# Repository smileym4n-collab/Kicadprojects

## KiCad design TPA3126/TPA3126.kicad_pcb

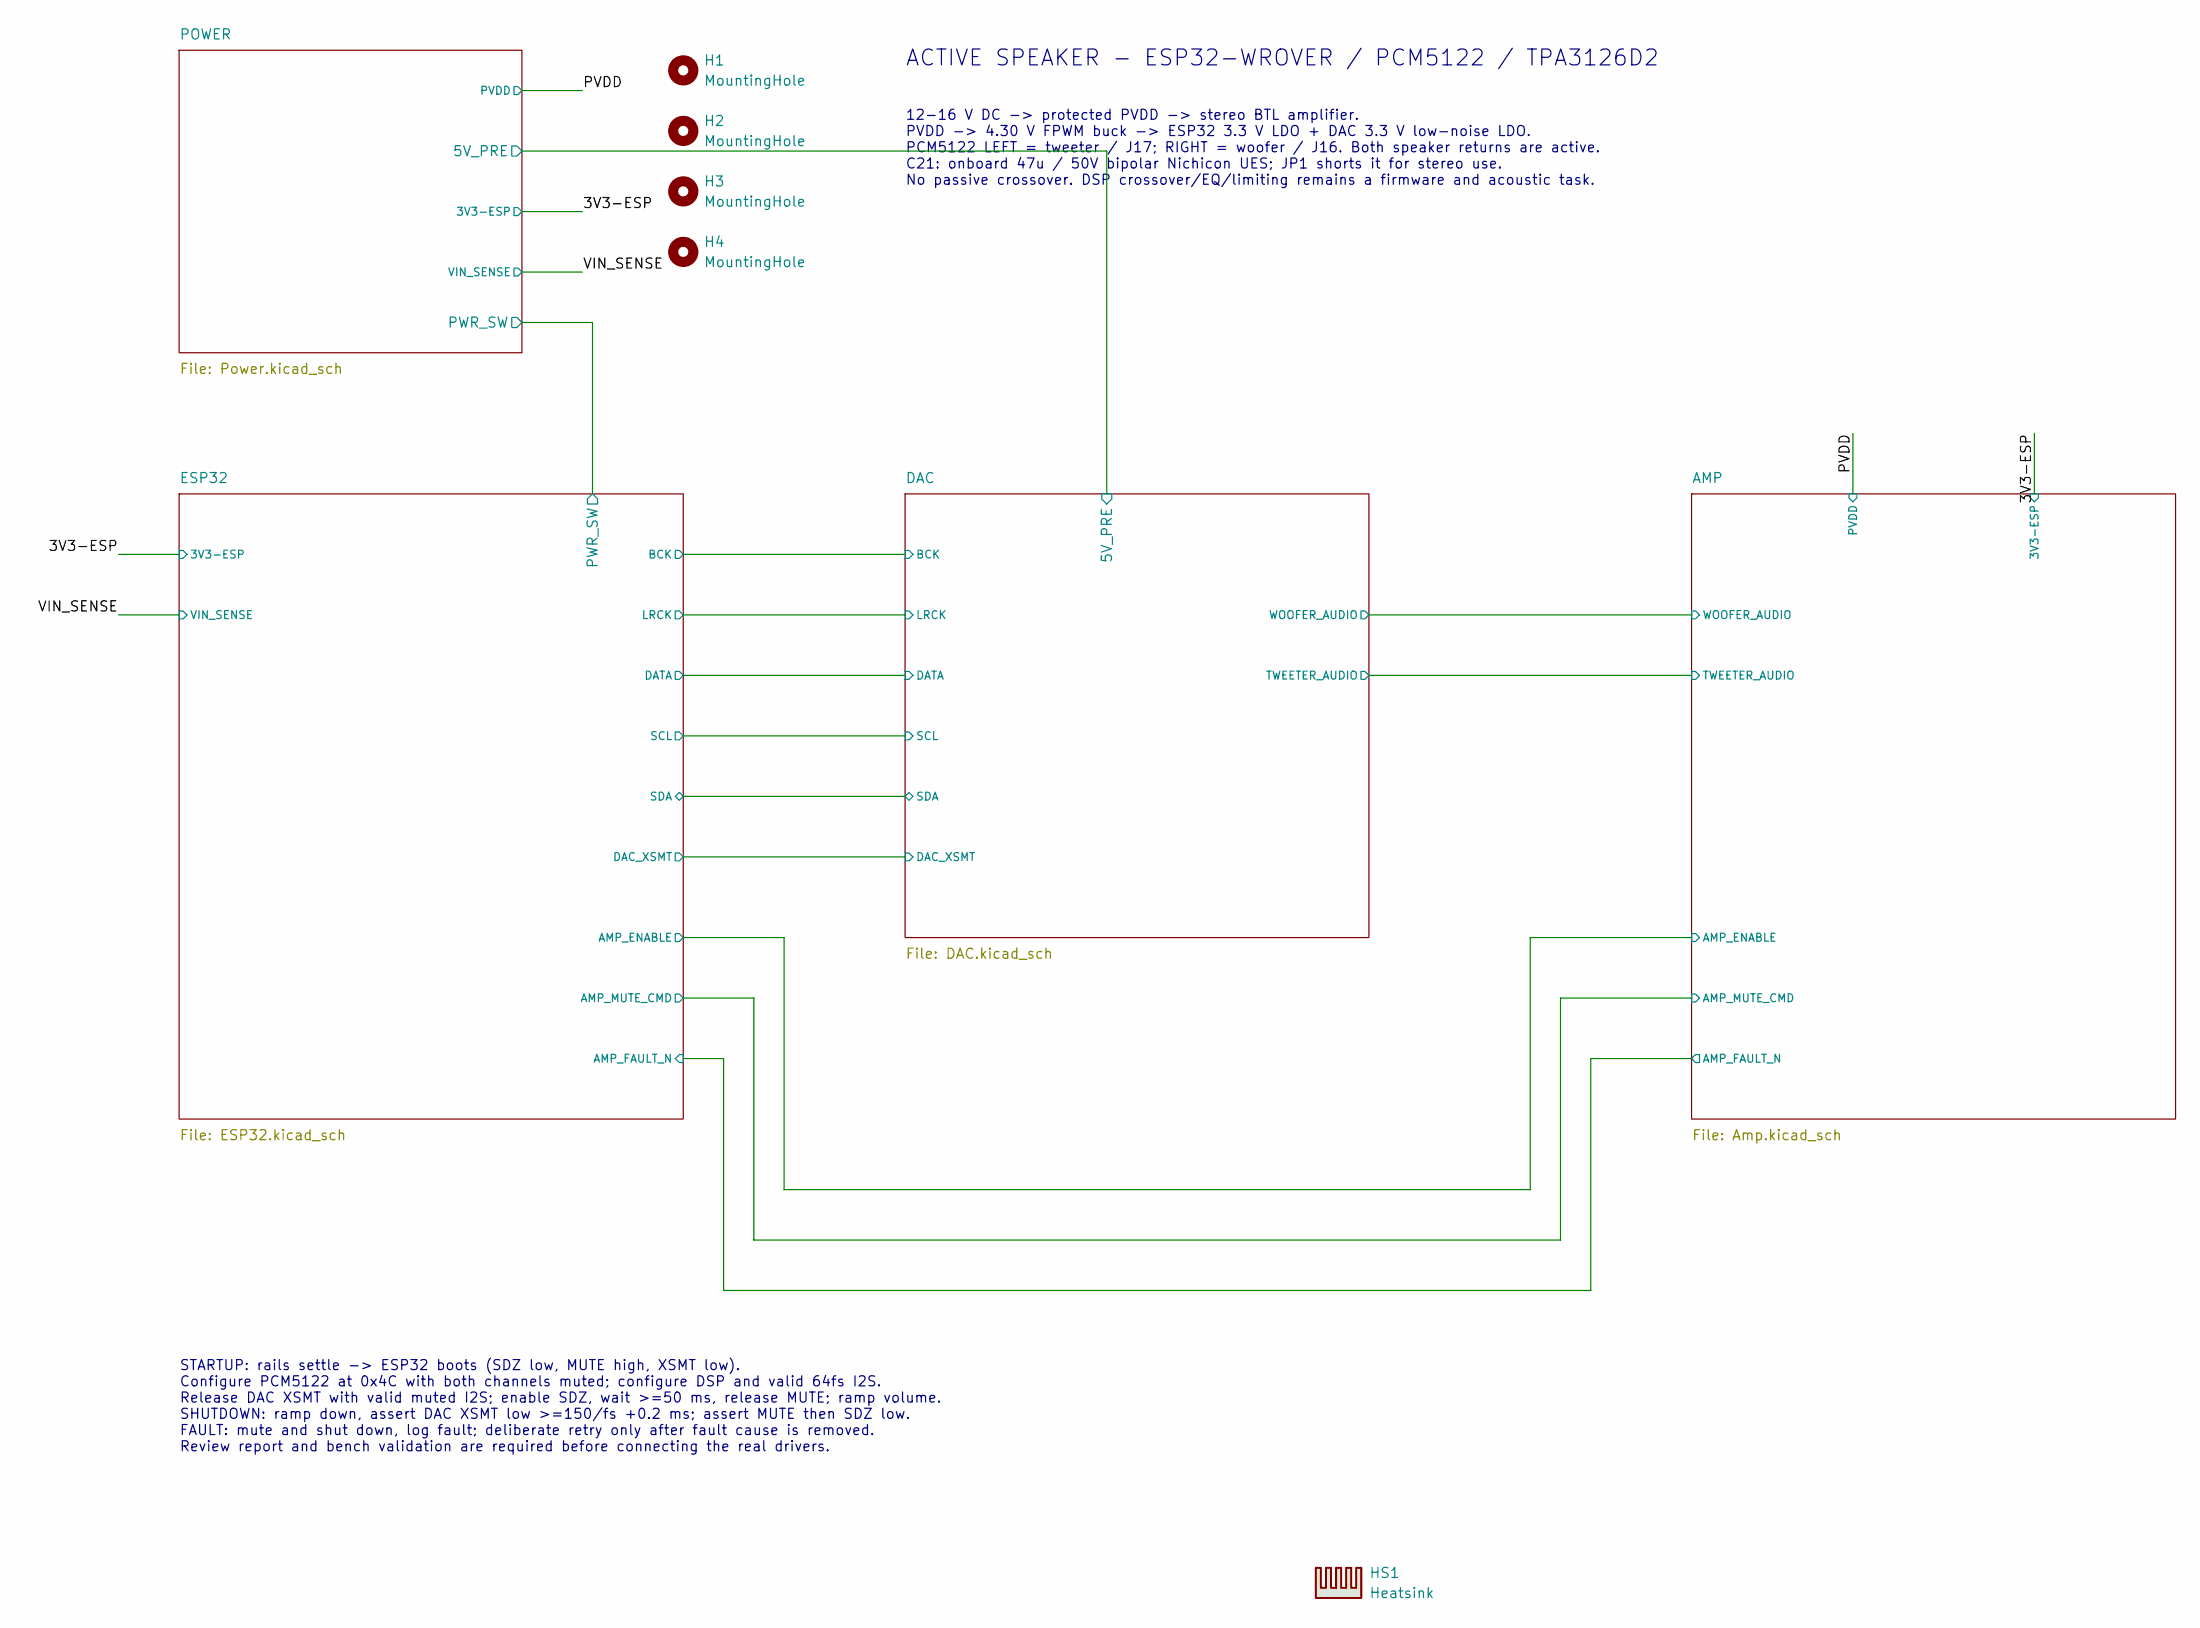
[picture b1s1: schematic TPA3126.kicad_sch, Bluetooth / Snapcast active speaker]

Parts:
H1, H2, H3, H4: MountingHole; MountingHole_3.2mm_M3
HS1: Heatsink; Heatsink_ATS_ATS-TI1OP-521-C1-R1_50x13.9mm_H25mm_P40mm; MPN ATS-TI1OP-521-C1-R1

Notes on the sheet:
STARTUP: rails settle -> ESP32 boots (SDZ low, MUTE high, XSMT low). Configure PCM5122 at 0x4C with both channels muted; configure DSP and valid 64fs I2S. Release DAC XSMT with valid muted I2S; enable SDZ, wait >=50 ms, release MUTE; ramp volume. SHUTDOWN: ramp down, assert DAC XSMT low >=150/fs +0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
ACTIVE SPEAKER - ESP32-WROVER / PCM5122 / TPA3126D2
12-16 V DC -> protected PVDD -> stereo BTL amplifier. PVDD -> 4.30 V FPWM buck -> ESP32 3.3 V LDO + DAC 3.3 V low-noise LDO. PCM5122 LEFT = tweeter / J17; RIGHT = woofer / J16. Both speaker returns are active. C21: onboard 47u / 50V bipolar Nichicon UES; JP1 shorts it for stereo use. No passive cro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

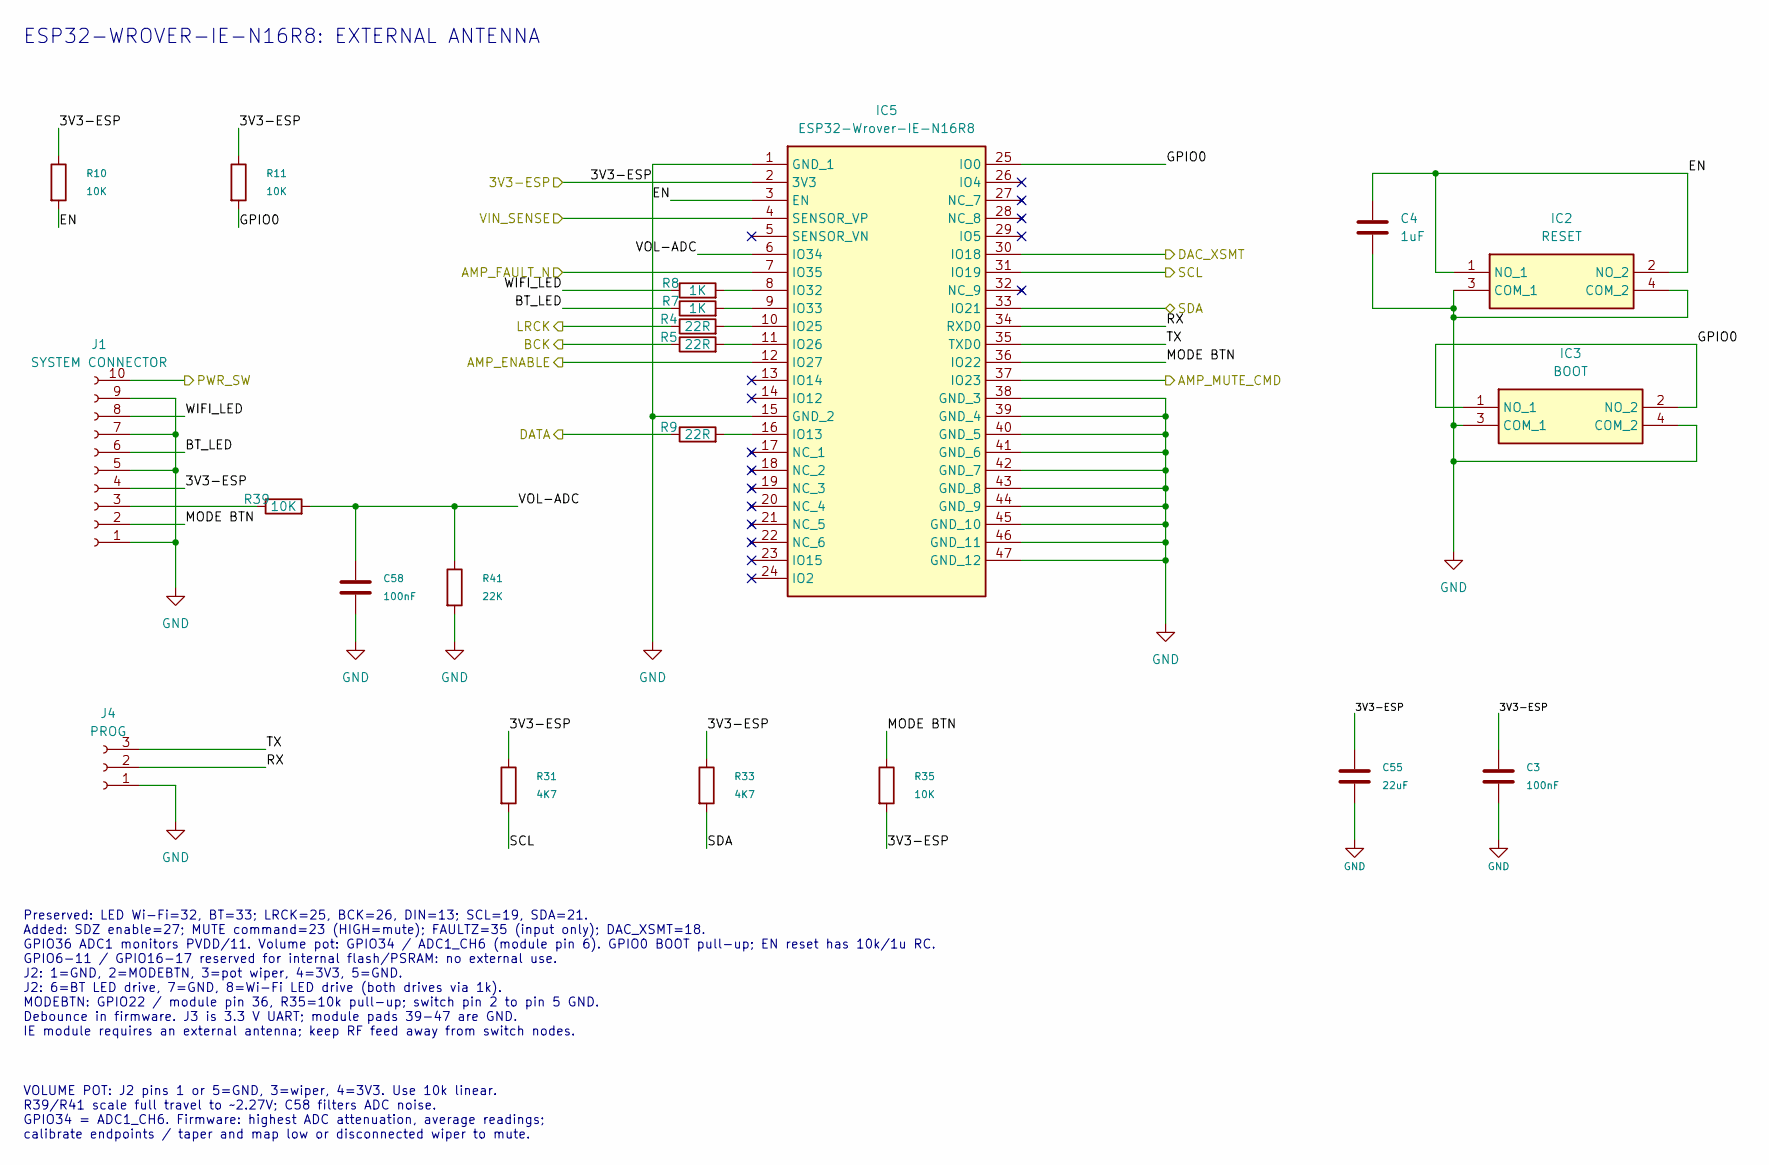
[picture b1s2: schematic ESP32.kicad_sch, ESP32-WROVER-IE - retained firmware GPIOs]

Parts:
C3, C58: 100nF; C_1206_3216Metric_Pad1.33x1.80mm_HandSolder; MPN C1206C104K5RACTU
C4: 1uF; C_1206_3216Metric_Pad1.33x1.80mm_HandSolder; MPN CL31B105KBHNFNE
C55: 22uF; C_1206_3216Metric_Pad1.33x1.80mm_HandSolder; MPN CL31A226KAHNNNE
IC2: RESET; TS026650BK100SCRD; Mouser Part Number 179-TS026650BK100SCR
IC3: BOOT; TS026650BK100SCRD; Mouser Part Number 179-TS026650BK100SCR
IC5: ESP32-Wrover-IE-N16R8; ESP32-WROVER-IE-N16R8; Mouser Part Number 356-ESP32WRVIE2864UC
J1: SYSTEM CONNECTOR; JST_XH_B10B-XH-A_1x10_P2.50mm_Vertical
J4: PROG; PinHeader_1x03_P2.54mm_Vertical
R4, R5, R9: 22R; R_0603_1608Metric_Pad0.98x0.95mm_HandSolder; MPN RK73B1JTTD220J
R7, R8: 1K; R_0805_2012Metric_Pad1.20x1.40mm_HandSolder; Manufacturer_Part_Number RMCF0805FT1K00
R10, R11, R35: 10K; R_0603_1608Metric_Pad0.98x0.95mm_HandSolder; Manufacturer_Part_Number RC0603FR-0710KL
R31, R33: 4K7; R_0805_2012Metric_Pad1.20x1.40mm_HandSolder; MPN RMCF0805FT4K70
R39: 10K; R_0805_2012Metric_Pad1.20x1.40mm_HandSolder; MPN RK73B2ATTD103J
R41: 22K; R_0805_2012Metric_Pad1.20x1.40mm_HandSolder; MPN RR1220P-223-D

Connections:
/3V3-ESP: C3.1, C55.1, IC5.2 (3V3), J1.4, R10.1, R11.1, R31.1, R33.1, R35.2; also elsewhere on the board
/AMP/AMP_ENABLE: IC5.12 (IO27); also elsewhere on the board
/AMP/AMP_FAULT_N: IC5.7 (IO35); also elsewhere on the board
/AMP/AMP_MUTE_CMD: IC5.37 (IO23); also elsewhere on the board
/DAC/BCK: R5.1; also elsewhere on the board
/DAC/DAC_XSMT: IC5.30 (IO18); also elsewhere on the board
/DAC/DATA: R9.1; also elsewhere on the board
/DAC/LRCK: R4.1; also elsewhere on the board
/ESP32/BT_LED: J1.6, R7.1
/ESP32/EN: C4.1, IC2.1 (NO_1), IC2.2 (NO_2), IC5.3 (EN), R10.2
/ESP32/GPIO0: IC3.1 (NO_1), IC3.2 (NO_2), IC5.25 (IO0), R11.2
/ESP32/MODE BTN: IC5.36 (IO22), J1.2, R35.1
/ESP32/PWR_SW: J1.10; also elsewhere on the board
/ESP32/RX: IC5.34 (RXD0), J4.2
/ESP32/SCL: IC5.31 (IO19), R31.2; also elsewhere on the board
/ESP32/SDA: IC5.33 (IO21), R33.2; also elsewhere on the board
/ESP32/TX: IC5.35 (TXD0), J4.3
/ESP32/VOL-ADC: C58.1, IC5.6 (IO34), R39.2, R41.1
/ESP32/WIFI_LED: J1.8, R8.1
/VIN_SENSE: IC5.4 (SENSOR_VP); also elsewhere on the board
GND: C3.2, C4.2, C55.2, C58.2, IC2.3 (COM_1), IC2.4 (COM_2), IC3.3 (COM_1), IC3.4 (COM_2), IC5.1 (GND_1), IC5.15 (GND_2), IC5.38 (GND_3), IC5.39 (GND_4), IC5.40 (GND_5), IC5.41 (GND_6), IC5.42 (GND_7), IC5.43 (GND_8), IC5.44 (GND_9), IC5.45 (GND_10), IC5.46 (GND_11), IC5.47 (GND_12), J1.1, J1.5, J1.7, J1.9, J4.1, R41.2; also elsewhere on the board
unnamed: IC5.16 (IO13), R9.2
unnamed: IC5.10 (IO25), R4.2
unnamed: IC5.11 (IO26), R5.2
unnamed: IC5.8 (IO32), R8.2
unnamed: IC5.9 (IO33), R7.2
unnamed: J1.3, R39.1

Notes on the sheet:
ESP32-WROVER-IE-N16R8: EXTERNAL ANTENNA
VOLUME POT: J2 pins 1 or 5=GND, 3=wiper, 4=3V3. Use 10k linear. R39/R41 scale full travel to ~2.27V; C58 filters ADC noise. GPIO34 = ADC1_CH6. Firmware: highest ADC attenuation, average readings; calibrate endpoints / taper and map low or disconnected wiper to mute.
Preserved: LED Wi-Fi=32, BT=33; LRCK=25, BCK=26, DIN=13; SCL=19, SDA=21. Added: SDZ enable=27; MUTE command=23 (HIGH=mute); FAULTZ=35 (input only); DAC_XSMT=18. GPIO36 ADC1 monitors PVDD/11. Volume pot: GPIO34 / ADC1_CH6 (module pin 6). GPIO0 BOOT pull-up; EN reset has 10k/1u RC. GPIO6-11 / GPIO16-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

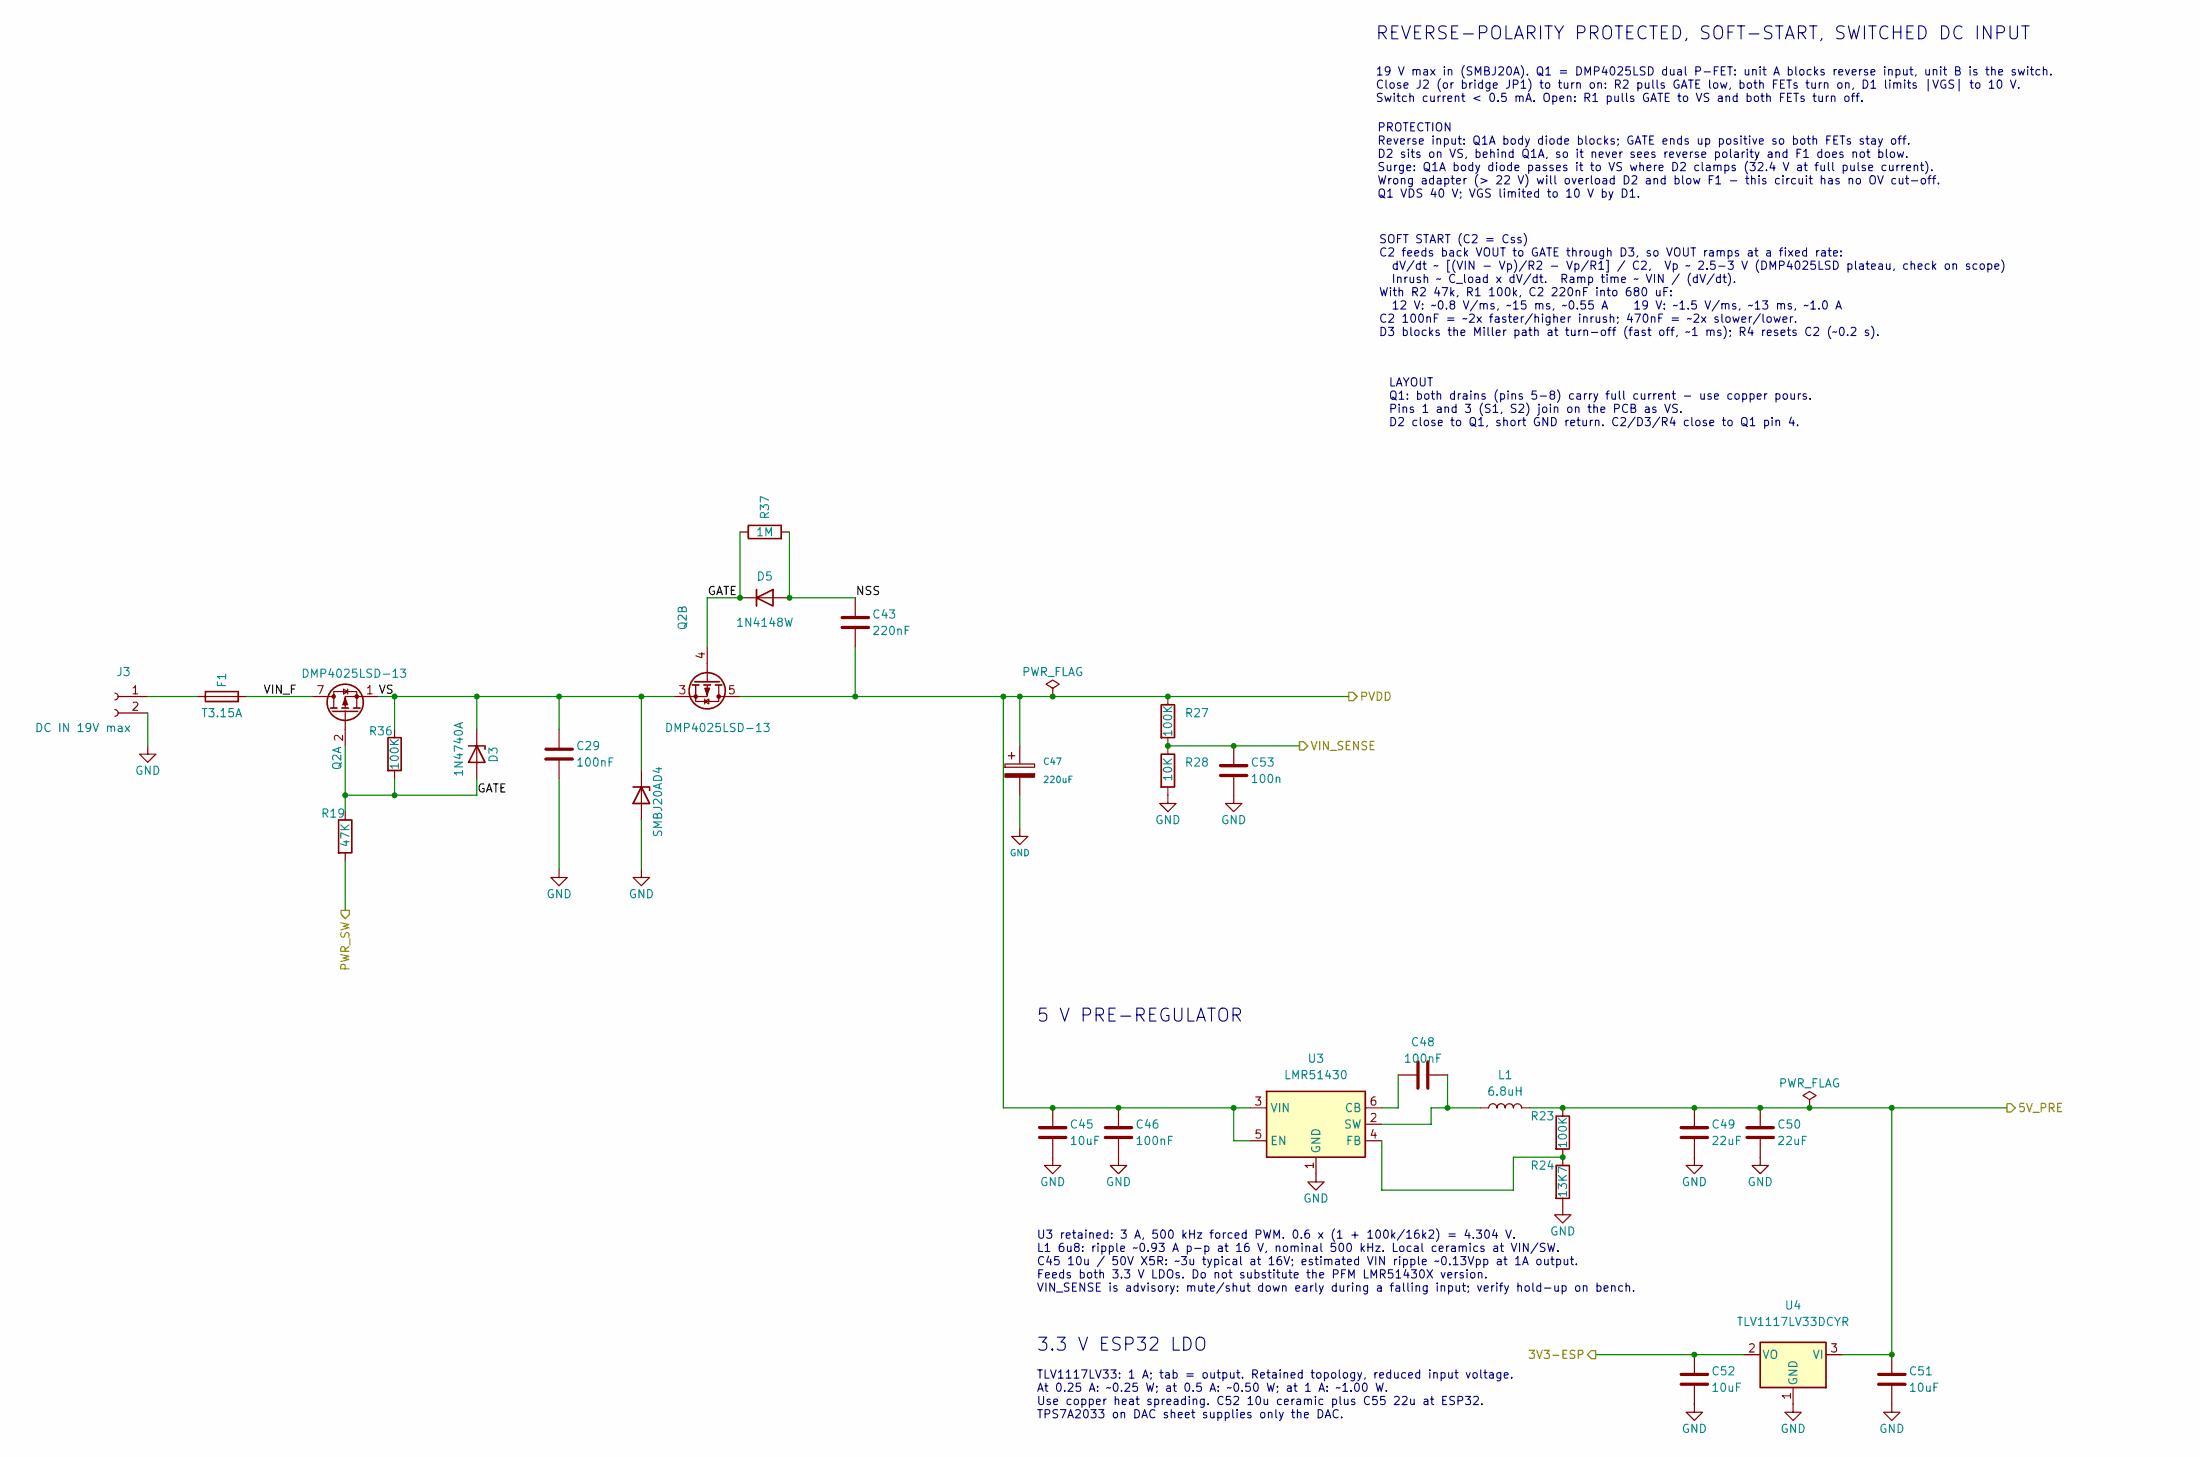
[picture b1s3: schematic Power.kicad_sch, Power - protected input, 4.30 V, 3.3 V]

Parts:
C29: 100nF; C_1206_3216Metric_Pad1.33x1.80mm_HandSolder; Manufacturer_Part_Number MC0805B104K500CT
C43: 220nF; C_0805_2012Metric_Pad1.18x1.45mm_HandSolder; Manufacturer_Part_Number CL21B224KBFNNNE
C45: 10uF; C_1206_3216Metric_Pad1.33x1.80mm_HandSolder; Voltage_Rating 50 V; Tolerance 10%; Manufacturer_Part_Number CL31A106KBHNNNE
C46, C48: 100nF; C_1206_3216Metric_Pad1.33x1.80mm_HandSolder; Manufacturer_Part_Number MC0603B104K500CT
C47: 220uF; CP_Radial_D8.0mm_P3.50mm; MPN 35ZLH220MEFC8X11.5
C49, C50: 22uF; C_1206_3216Metric_Pad1.33x1.80mm_HandSolder; Manufacturer_Part_Number CL31A226KAHNNNE
C51, C52: 10uF; C_0805_2012Metric_Pad1.18x1.45mm_HandSolder; Manufacturer_Part_Number CL21A106KOQNNNF
C53: 100n; C_0603_1608Metric_Pad1.08x0.95mm_HandSolder; Manufacturer_Part_Number MC0603B104K500CT
D3: 1N4740A; D_DO-41_SOD81_P10.16mm_Horizontal; Manufacturer_Part_Number 1N4740ATR
D4: SMBJ20A; D_SMB; Manufacturer_Part_Number SMBJ20A
D5: 1N4148W; D_SOD-123; Manufacturer_Part_Number 1N4148W
F1: T3.15A; Fuse_Littelfuse_395Series; Manufacturer_Part_Number 39213150000
J3: DC IN 19V max; Molex_KK-396_5273-02A_1x02_P3.96mm_Vertical; Manufacturer_Part_Number 09-65-2028
L1: 6.8uH; SRP6030WA-6R8M; Manufacturer_Part_Number SRP6030WA-6R8M
Q2: DMP4025LSD-13; SOIC-8_3.9x4.9mm_P1.27mm; Manufacturer_Part_Number DMP4025LSD-13
R19: 47K; R_0805_2012Metric_Pad1.20x1.40mm_HandSolder; Manufacturer_Part_Number RC0805FR-0747KL
R23, R27: 100K; R_0805_2012Metric_Pad1.20x1.40mm_HandSolder; Manufacturer_Part_Number RC0603FR-07100KL
R24: 13K7; R_0805_2012Metric_Pad1.20x1.40mm_HandSolder; Manufacturer_Part_Number RC0603FR-0716K2L
R28: 10K; R_0603_1608Metric_Pad0.98x0.95mm_HandSolder; Manufacturer_Part_Number RC0603FR-0710KL
R36: 100K; R_0805_2012Metric_Pad1.20x1.40mm_HandSolder; Manufacturer_Part_Number RC0805FR-07100KL
R37: 1M; R_0805_2012Metric_Pad1.20x1.40mm_HandSolder; Manufacturer_Part_Number RC0805FR-071ML
U3: LMR51430; TSOT-23-6; Manufacturer_Part_Number LMR51430XFDDCR
U4: TLV1117LV33DCYR; SOT-223-3_TabPin2; Manufacturer_Part_Number TS1117B

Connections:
/3V3-ESP: C52.1, U4.2 (VO); also elsewhere on the board
/DAC/5V_PRE: C49.1, C50.1, C51.1, L1.2, R23.1, U4.3 (VI); also elsewhere on the board
/ESP32/PWR_SW: R19.2; also elsewhere on the board
/POWER/GATE: D3.2 (A), D5.1 (K), Q2.2 (G), Q2.4 (G), R19.1, R36.2, R37.1
/POWER/NSS: C43.1, D5.2 (A), R37.2
/POWER/VIN_F: F1.2, Q2.7 (D), Q2.8 (D)
/POWER/VS: C29.1, D3.1 (K), D4.1 (K), Q2.1 (S), Q2.3 (S), R36.1
/PVDD: C43.2, C45.1, C46.1, C47.1, Q2.5 (D), Q2.6 (D), R27.1, U3.3 (VIN), U3.5 (EN); also elsewhere on the board
/VIN_SENSE: C53.1, R27.2, R28.1; also elsewhere on the board
GND: C29.2, C45.2, C46.2, C47.2, C49.2, C50.2, C51.2, C52.2, C53.2, D4.2 (A), J3.2, R24.2, R28.2, U3.1 (GND), U4.1 (GND); also elsewhere on the board
unnamed: F1.1, J3.1
unnamed: C48.1, U3.6 (CB)
unnamed: R23.2, R24.1, U3.4 (FB)
unnamed: C48.2, L1.1, U3.2 (SW)

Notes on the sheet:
SOFT START (C2 = Css) C2 feeds back VOUT to GATE through D3, so VOUT ramps at a fixed rate: dV/dt ~ [(VIN - Vp)/R2 - Vp/R1] / C2, Vp ~ 2.5-3 V (DMP4025LSD plateau, check on scope) Inrush ~ C_load x dV/dt. Ramp time ~ VIN / (dV/dt). With R2 47k, R1 100k, C2 220nF into 680 uF: 12 V: ~0.8 V/ms, ~15 ms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
5 V PRE-REGULATOR
LAYOUT Q1: both drains (pins 5-8) carry full current - use copper pours. Pins 1 and 3 (S1, S2) join on the PCB as VS. D2 close to Q1, short GND return. C2/D3/R4 close to Q1 pin 4.
3.3 V ESP32 LDO
PROTECTION Reverse input: Q1A body diode blocks; GATE ends up positive so both FETs stay off. D2 sits on VS, behind Q1A, so it never sees reverse polarity and F1 does not blow. Surge: Q1A body diode passes it to VS where D2 clamps (32.4 V at full pulse current). Wrong adapter (> 22 V) will overload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
REVERSE-POLARITY PROTECTED, SOFT-START, SWITCHED DC INPUT
U3 retained: 3 A, 500 kHz forced PWM. 0.6 x (1 + 100k/16k2) = 4.304 V. L1 6u8: ripple ~0.93 A p-p at 16 V, nominal 500 kHz. Local ceramics at VIN/SW. C45 10u / 50V X5R: ~3u typical at 16V; estimated VIN ripple ~0.13Vpp at 1A output. Feeds both 3.3 V LDOs. Do not substitute the PFM LMR51430X version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
19 V max in (SMBJ20A). Q1 = DMP4025LSD dual P-FET: unit A blocks reverse input, unit B is the switch. Close J2 (or bridge JP1) to turn on: R2 pulls GATE low, both FETs turn on, D1 limits |VGS| to 10 V. Switch current < 0.5 mA. Open: R1 pulls GATE to VS and both FETs turn off.
TLV1117LV33: 1 A; tab = output. Retained topology, reduced input voltage. At 0.25 A: ~0.25 W; at 0.5 A: ~0.50 W; at 1 A: ~1.00 W. Use copper heat spreading. C52 10u ceramic plus C55 22u at ESP32. TPS7A2033 on DAC sheet supplies only the DAC.

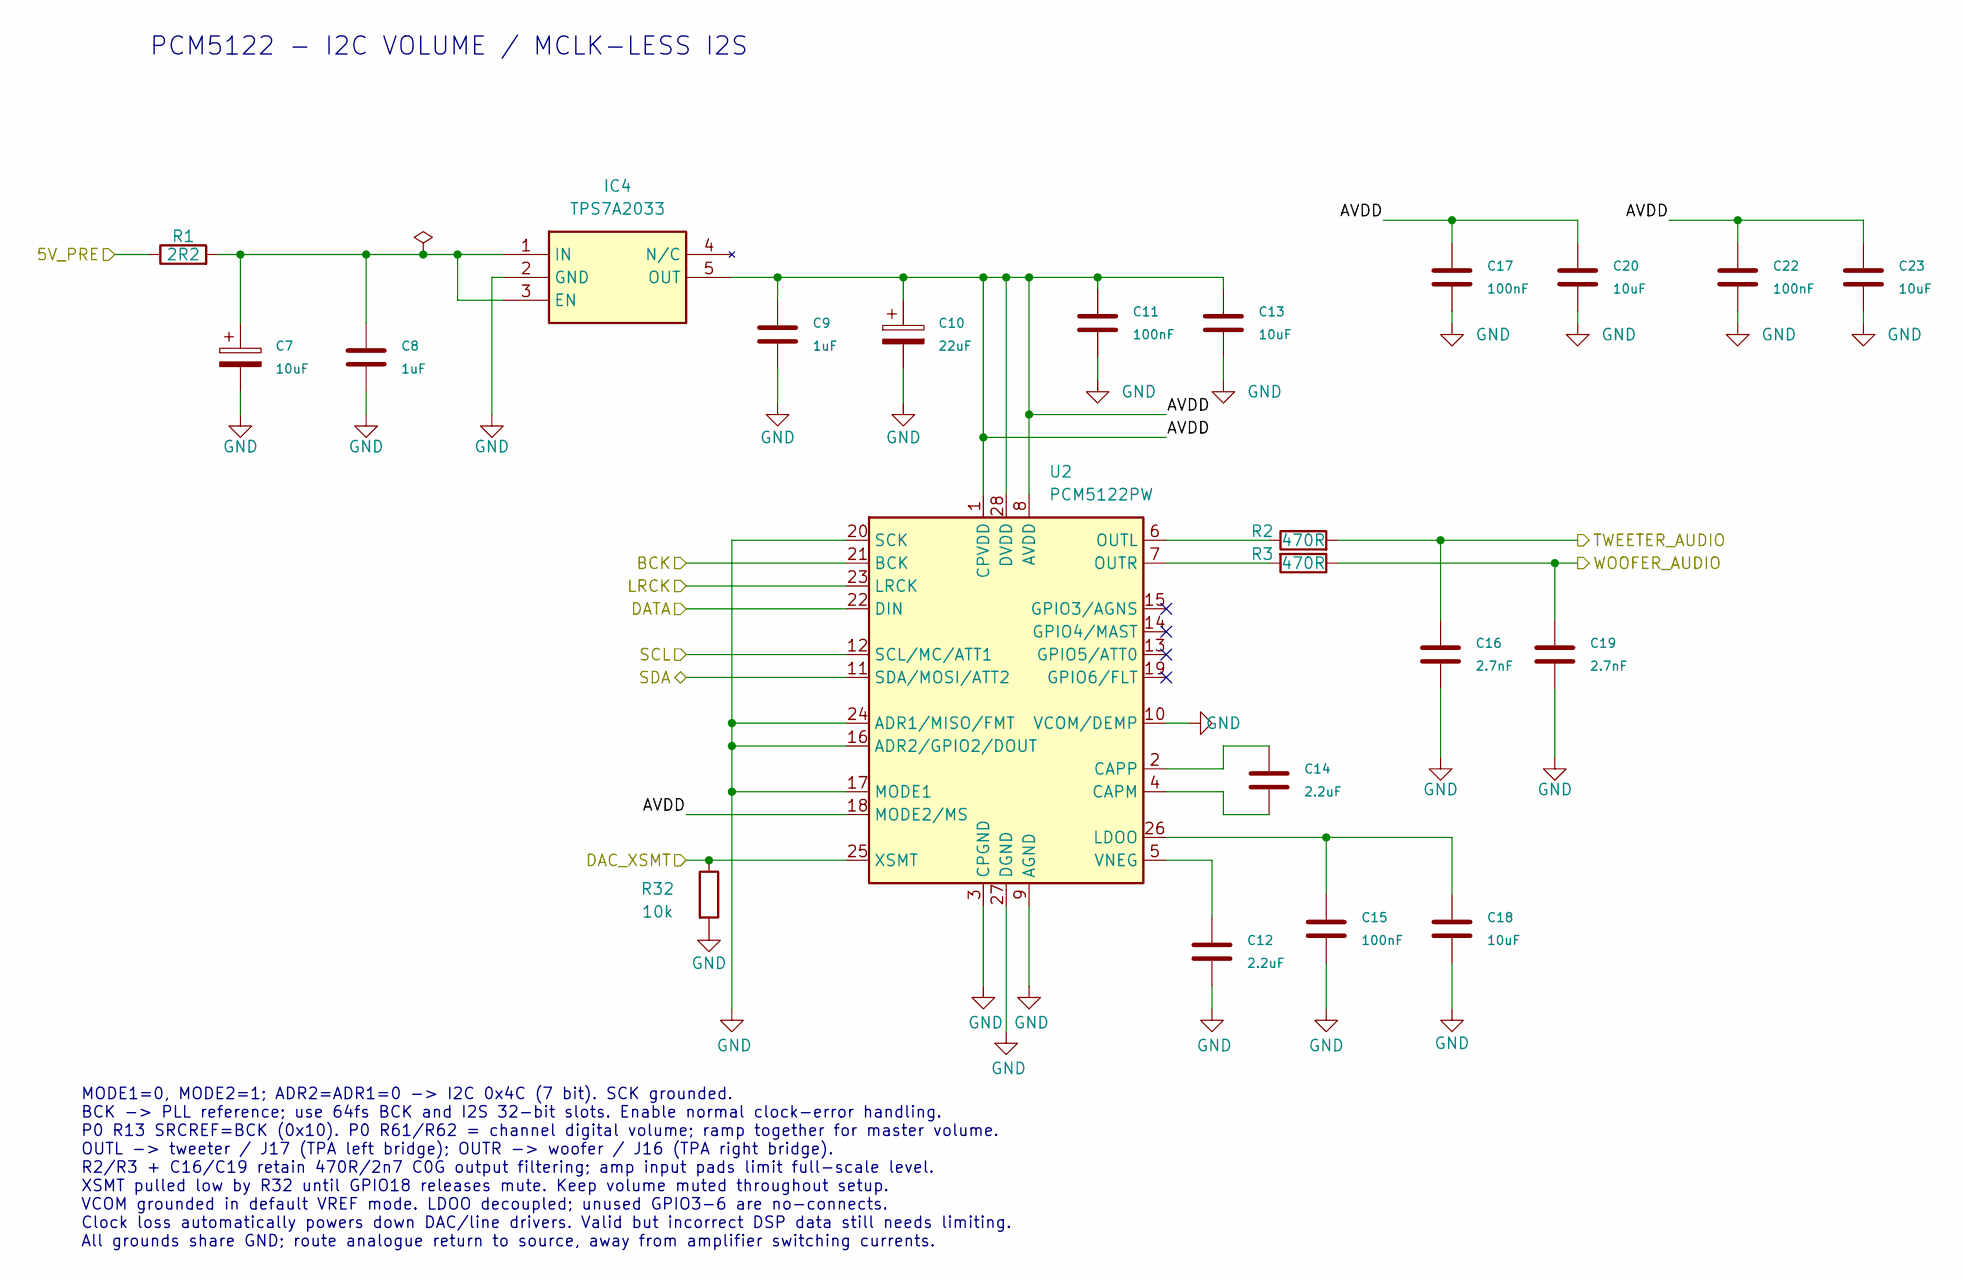
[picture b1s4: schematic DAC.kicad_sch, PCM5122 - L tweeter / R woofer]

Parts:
C7: 10uF; CP_Radial_D5.0mm_P2.00mm; MPN UFW1H100MDD
C8, C9: 1uF; C_1206_3216Metric_Pad1.33x1.80mm_HandSolder; MPN CL31B105KBHNFNE
C10: 22uF; CP_Radial_D5.0mm_P2.00mm; MPN UFW1E220MDD
C11, C15, C17, C22: 100nF; C_1206_3216Metric_Pad1.33x1.80mm_HandSolder; MPN C1206C104K5RACTU
C12, C14: 2.2uF; C_0805_2012Metric_Pad1.18x1.45mm_HandSolder; MPN CL21B225KPFNNNE
C13, C20, C23: 10uF; C_0805_2012Metric_Pad1.18x1.45mm_HandSolder; MPN CL21A106KOQNNNF
C16, C19: 2.7nF; C_0805_2012Metric_Pad1.18x1.45mm_HandSolder; MPN 0805N272J500CT
C18: 10uF; C_1206_3216Metric_Pad1.33x1.80mm_HandSolder; MPN TMK316B7106KL-TD
IC4: TPS7A2033; SOT95P280X145-5N; Mouser Part Number 595-TPS7A2033PDBVR
R1: 2R2; R_0805_2012Metric_Pad1.20x1.40mm_HandSolder; Manufacturer_Part_Number MCWR08W2R20FTL
R2, R3: 470R; R_0805_2012Metric_Pad1.20x1.40mm_HandSolder; Manufacturer_Part_Number RR1220P-471-D
R32: 10k; R_0603_1608Metric_Pad0.98x0.95mm_HandSolder; Manufacturer_Part_Number RC0603FR-0710KL
U2: PCM5122PW; TSSOP-28_4.4x9.7mm_P0.65mm; MPN PCM5122PWR

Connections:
/AMP/TWEETER_AUDIO: C16.1, R2.2; also elsewhere on the board
/AMP/WOOFER_AUDIO: C19.1, R3.1; also elsewhere on the board
/DAC/5V_PRE: R1.1; also elsewhere on the board
/DAC/AVDD: C9.1, C10.1, C11.1, C13.1, C17.1, C20.1, C22.1, C23.1, IC4.5 (OUT), U2.1 (CPVDD), U2.8 (AVDD), U2.18 (MODE2/MS), U2.28 (DVDD)
/DAC/BCK: U2.21 (BCK); also elsewhere on the board
/DAC/DAC_XSMT: R32.1, U2.25 (XSMT); also elsewhere on the board
/DAC/DATA: U2.22 (DIN); also elsewhere on the board
/DAC/LRCK: U2.23 (LRCK); also elsewhere on the board
/ESP32/SCL: U2.12 (SCL/MC/ATT1); also elsewhere on the board
/ESP32/SDA: U2.11 (SDA/MOSI/ATT2); also elsewhere on the board
GND: C7.2, C8.2, C9.2, C10.2, C11.2, C12.2, C13.2, C15.2, C16.2, C17.2, C18.2, C19.2, C20.2, C22.2, C23.2, IC4.2 (GND), R32.2, U2.3 (CPGND), U2.9 (AGND), U2.10 (VCOM/DEMP), U2.16 (ADR2/GPIO2/DOUT), U2.17 (MODE1), U2.20 (SCK), U2.24 (ADR1/MISO/FMT), U2.27 (DGND); also elsewhere on the board
unnamed: C7.1, C8.1, IC4.1 (IN), IC4.3 (EN), R1.2
unnamed: C14.2, U2.4 (CAPM)
unnamed: C14.1, U2.2 (CAPP)
unnamed: C15.1, C18.1, U2.26 (LDOO)
unnamed: R2.1, U2.6 (OUTL)
unnamed: R3.2, U2.7 (OUTR)
unnamed: C12.1, U2.5 (VNEG)

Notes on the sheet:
MODE1=0, MODE2=1; ADR2=ADR1=0 -> I2C 0x4C (7 bit). SCK grounded. BCK -> PLL reference; use 64fs BCK and I2S 32-bit slots. Enable normal clock-error handling. P0 R13 SRCREF=BCK (0x10). P0 R61/R62 = channel digital volume; ramp together for master volume. OUTL -> tweeter / J17 (TPA left bridge); OUTR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
PCM5122 - I2C VOLUME / MCLK-LESS I2S

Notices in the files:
ESPUSBI2S/ESPUSBI2S.kicad_pcb:
© Tom Watson Audio 2026
